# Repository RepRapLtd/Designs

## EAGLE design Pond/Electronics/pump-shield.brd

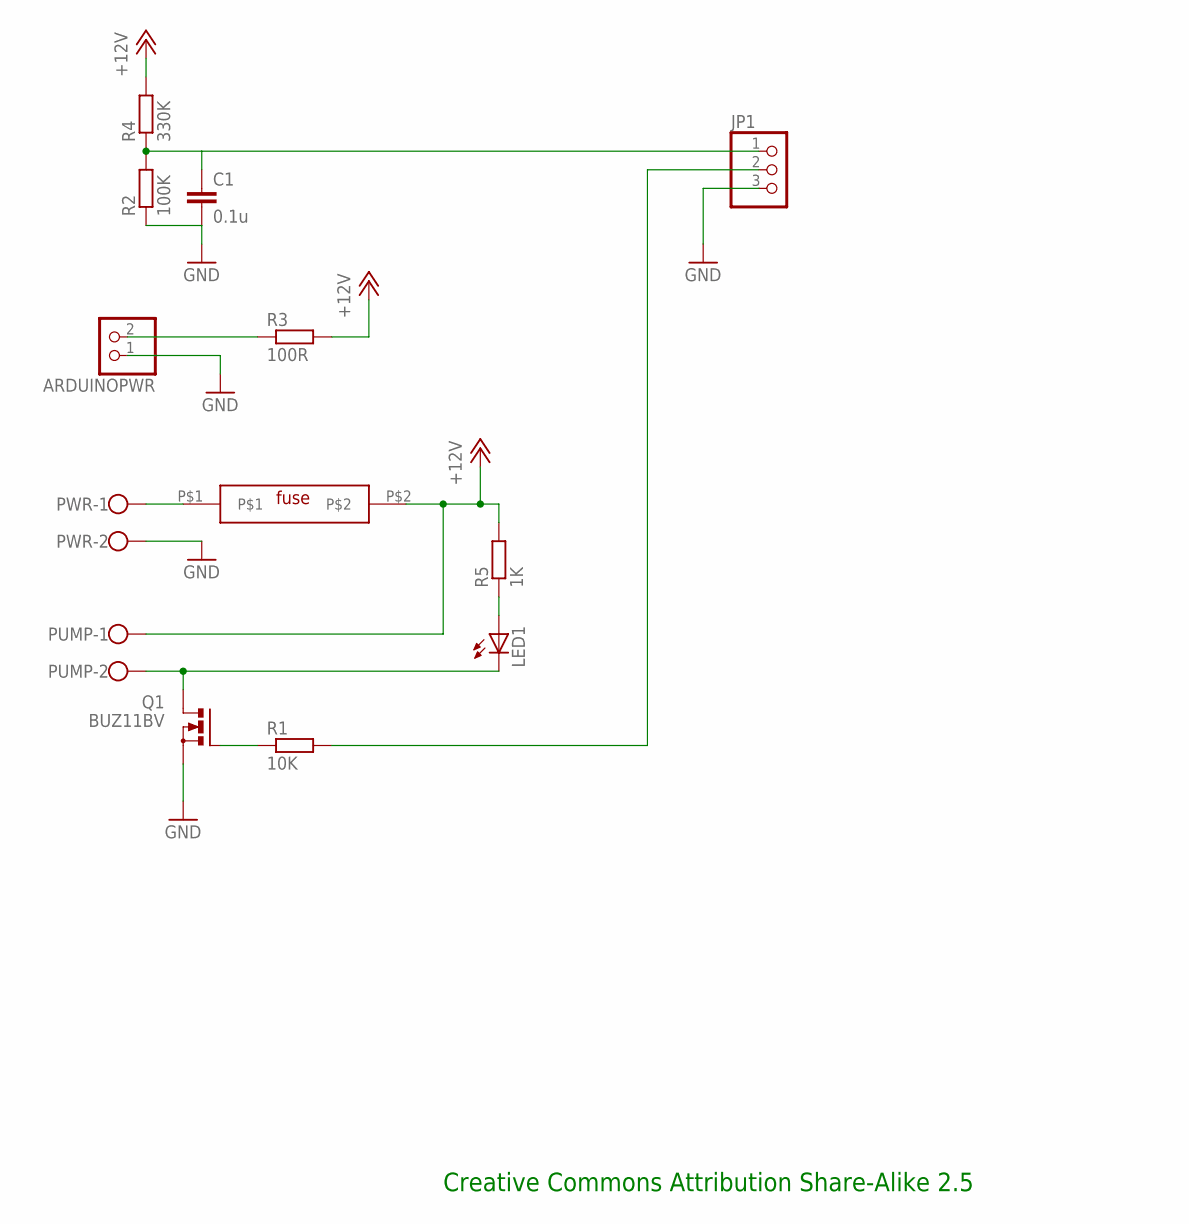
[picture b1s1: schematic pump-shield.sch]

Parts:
ARDUINOPWR: PINHD-1X2; 1X02
C1: 0.1u; C1608
JP1: PINHD-1X3; 1X03
LED1: LED5MM
PUMP: W237-102
PWR: W237-102
Q1: BUZ11BV; TO220BV
R1: 10K; R0603
R2: 100K; R0603
R3: 100R; 0204/7
R4: 330K; R0603
R5: 1K; R0603
U$1: 10A fuse; FUSE

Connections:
+12V: PUMP.1, R3.2, R4.2, R5.2, U$1.P$2
A5: C1.1, JP1.1, R2.2, R4.1
DIG2: JP1.2, R1.2
GND: ARDUINOPWR.1, C1.2, JP1.3, PWR.2, Q1.S, R2.1
unnamed: LED1.K (C), PUMP.2, Q1.D
unnamed: PWR.1, U$1.P$1
unnamed: Q1.G, R1.1
unnamed: ARDUINOPWR.2, R3.1
unnamed: LED1.A, R5.1

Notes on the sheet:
Creative Commons Attribution Share-Alike 2.5

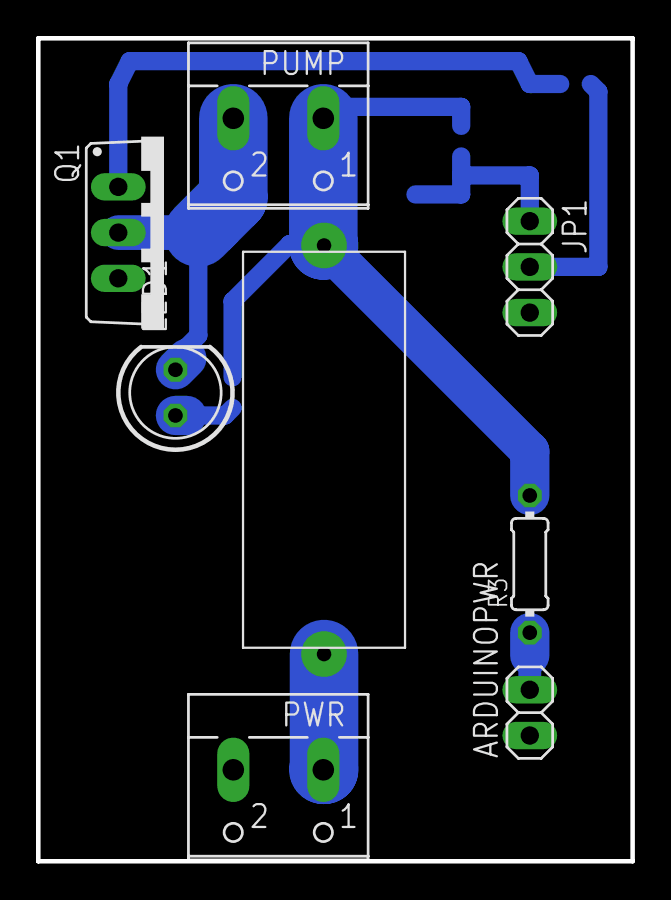
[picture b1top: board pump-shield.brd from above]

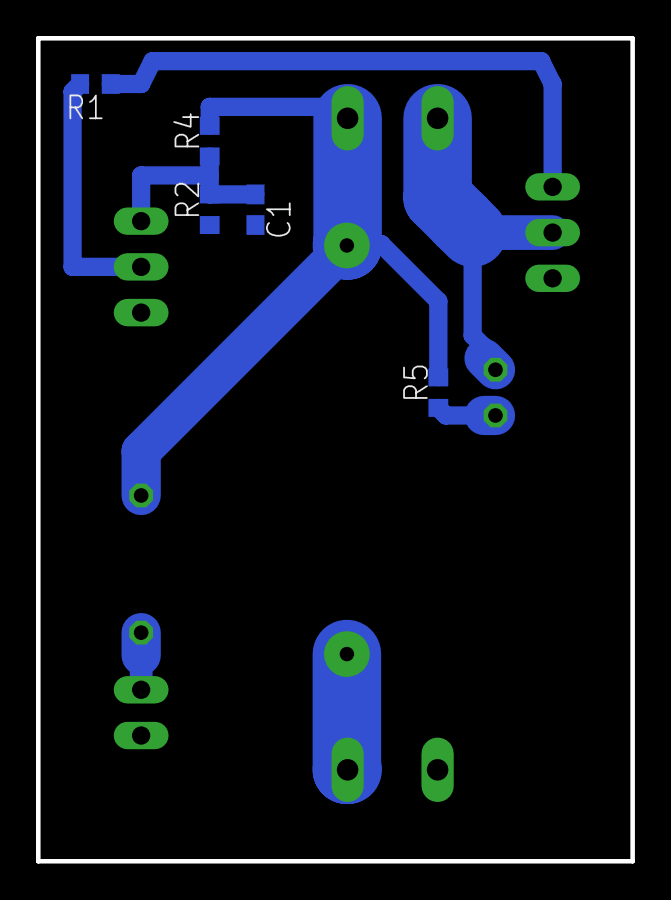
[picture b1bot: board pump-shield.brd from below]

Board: 2 copper layers, 33.0 x 45.7 mm, 13 parts (5 on the bottom side), 9 nets.
